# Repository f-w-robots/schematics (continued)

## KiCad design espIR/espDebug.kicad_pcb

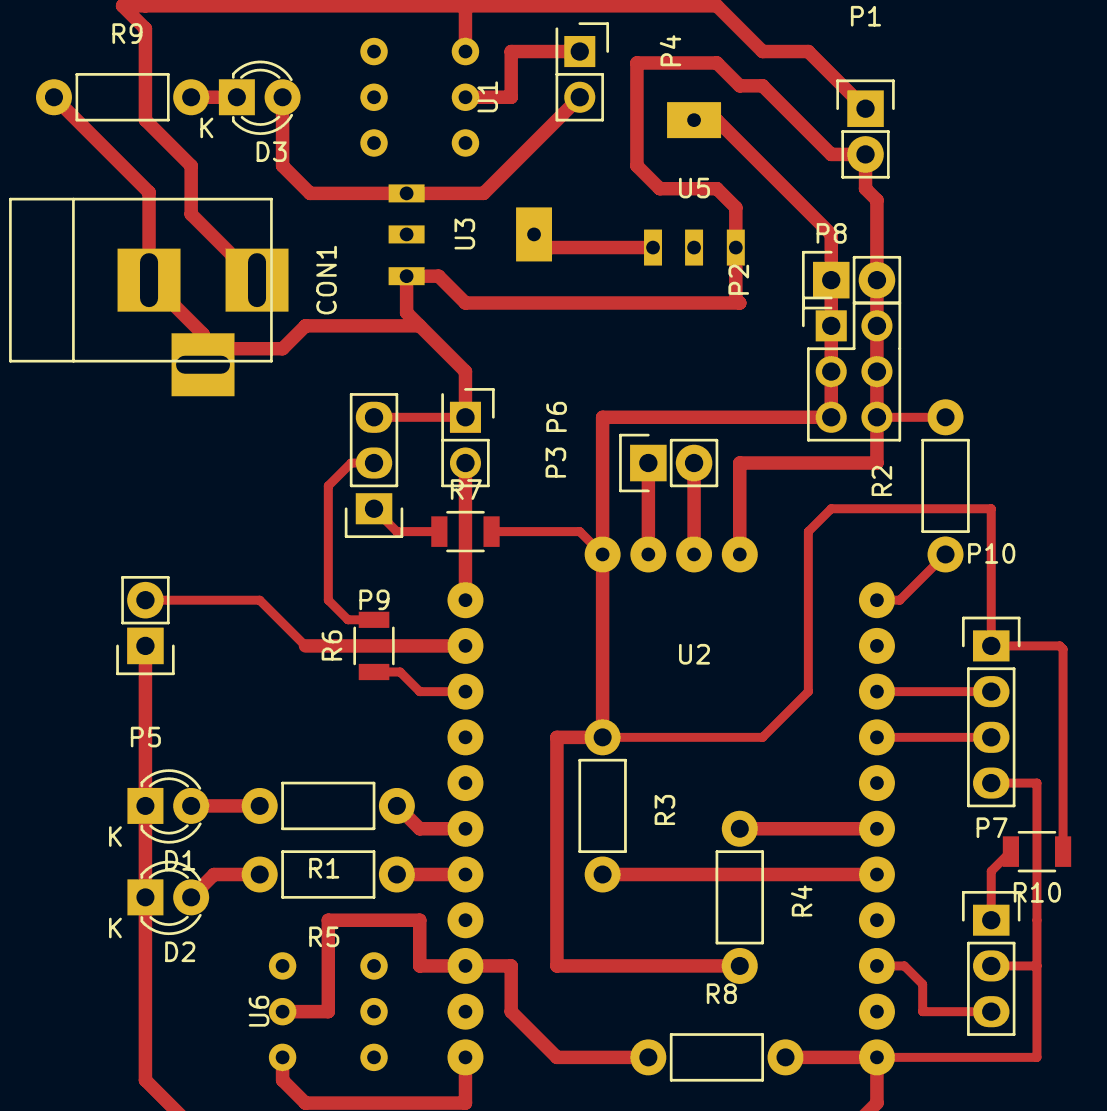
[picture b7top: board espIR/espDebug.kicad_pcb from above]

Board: 2 copper layers, 29 parts (0 on the bottom side), 28 nets.

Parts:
CON1: BARREL_JACK
D1, D2, D3: LED; LED-3MM
P1, P5: CONN_01X02; Pin_Header_Straight_1x02
P2: 3V3; Pin_Header_Straight_1x02
P3: RX/TX; Pin_Header_Straight_1x02
P4, P6: ON/OFF; Pin_Header_Straight_2x01
P7, P9: CONN_01X03; Pin_Header_Straight_1x03
P8: 3V3/GND; Pin_Header_Straight_2x03
P10: CONN_01X04; Pin_Header_Straight_1x04
R1, R5: R; Resistor_Horizontal_RM7mm
R2, R3, R4, R8: 10k; Resistor_Horizontal_RM7mm
R6, R7, R10: R; R_1206
R9: 1k; Resistor_Horizontal_RM7mm
U1: BUTTON; button
U2: ESP-201; ESP201
U3: AP1117-5; SMD-stab
U5: AP1117-3; SMD-stab
U6: button

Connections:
unnamed: CON1.1, P1.1, U1.1
unnamed: CON1.2, CON1.3, P1.2, P2.2, P6.1, P8.2, P8.4, P8.6, P9.3, R2.2, R9.1, U2.4, U3.1, U5.1
unnamed: D1.1, D2.1, P5.1, P7.2, P10.4, R8.2, U2.16
unnamed: D1.2, R1.2
unnamed: D2.2, R5.2
unnamed: D3.1, R9.2
unnamed: D3.2, P4.2, U3.3
unnamed: P3.1, U2.2
unnamed: P3.2, U2.3
unnamed: P4.1, U1.2
unnamed: P5.2, U2.6
unnamed: P6.2, U2.5
unnamed: P7.1, R10.2
unnamed: P7.3, U2.18
unnamed: P9.1, R7.1
unnamed: P9.2, R6.2
unnamed: P2.1, P8.1, P8.3, P8.5, P10.1, R3.1, R4.2, R7.2, R10.1, U2.1, U5.2
unnamed: P10.2, U2.24
unnamed: P10.3, U2.23
unnamed: R1.1, U2.10
unnamed: R2.1, U2.26
unnamed: R3.2, U2.20
unnamed: R4.1, U2.21
unnamed: R5.1, U2.11
unnamed: R6.1, U2.7
unnamed: R8.1, U2.13, U6.2
unnamed: U2.15, U6.1
unnamed: U3.2, U5.3

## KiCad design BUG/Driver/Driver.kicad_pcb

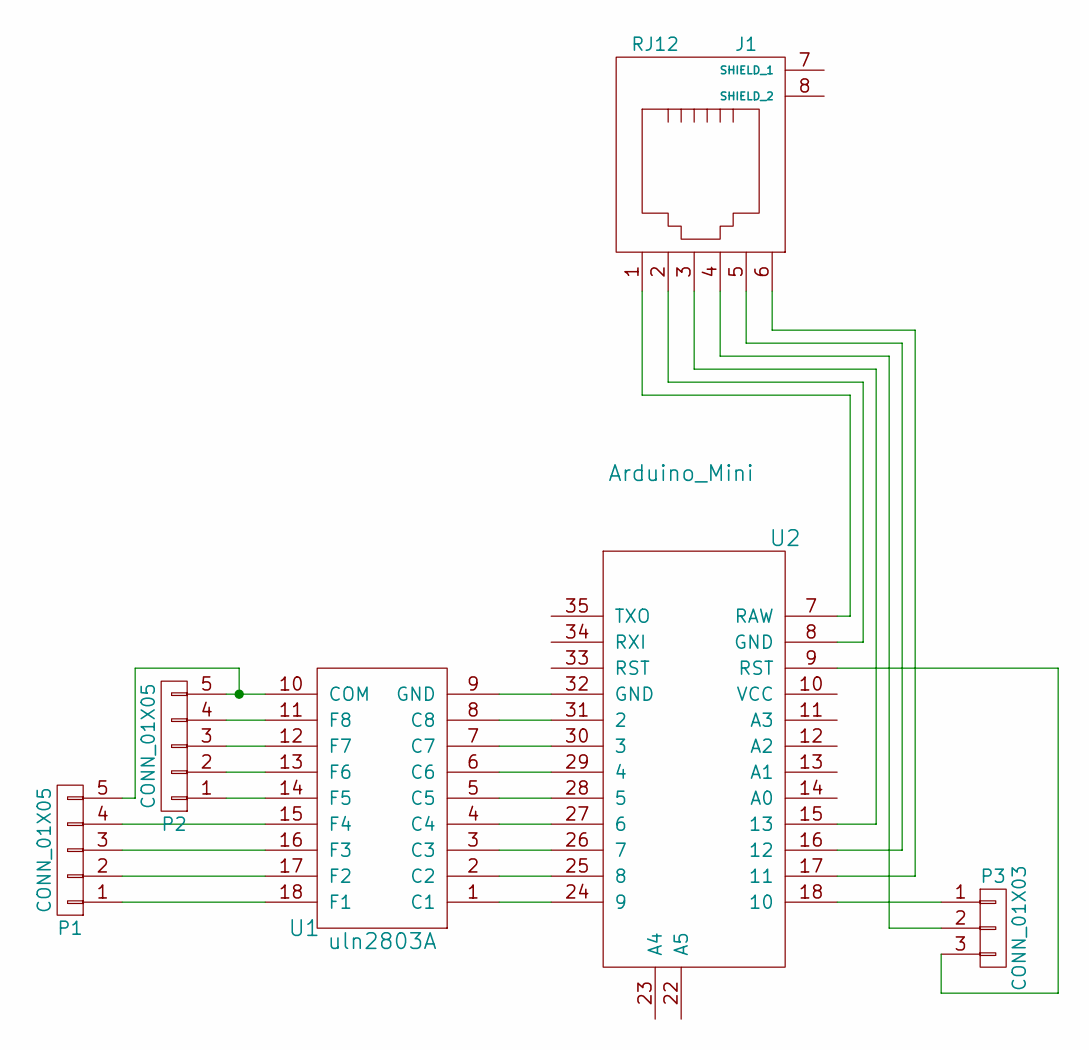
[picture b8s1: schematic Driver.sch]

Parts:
J1: RJ12; RJ12_Client
P1, P2: CONN_01X05; Pin_Header_Straight_1x05
P3: CONN_01X03; Pin_Header_Straight_1x03
U1: uln2803A; DIP-18_W7.62mm
U2: Arduino_Mini; arduino_mini_pro

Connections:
unnamed: J1.1, U2.7 (RAW)
unnamed: J1.2, U2.8 (GND)
unnamed: J1.3, U2.15 (13)
unnamed: J1.4, P3.2
unnamed: J1.5, U2.16 (12)
unnamed: J1.6, U2.17 (11)
unnamed: P1.1, U1.18 (F1)
unnamed: P1.2, U1.17 (F2)
unnamed: P1.3, U1.16 (F3)
unnamed: P1.4, U1.15 (F4)
unnamed: P1.5, P2.5, U1.10 (COM)
unnamed: P2.1, U1.14 (F5)
unnamed: P2.2, U1.13 (F6)
unnamed: P2.3, U1.12 (F7)
unnamed: P2.4, U1.11 (F8)
unnamed: P3.1, U2.18 (10)
unnamed: P3.3, U2.9 (RST)
unnamed: U1.1 (C1), U2.24 (9)
unnamed: U1.2 (С2), U2.25 (8)
unnamed: U1.3 (С3), U2.26 (7)
unnamed: U1.4 (С4), U2.27 (6)
unnamed: U1.5 (С5), U2.28 (5)
unnamed: U1.6 (С6), U2.29 (4)
unnamed: U1.7 (С7), U2.30 (3)
unnamed: U1.8 (С8), U2.31 (2)
unnamed: U1.9 (GND), U2.32 (GND)

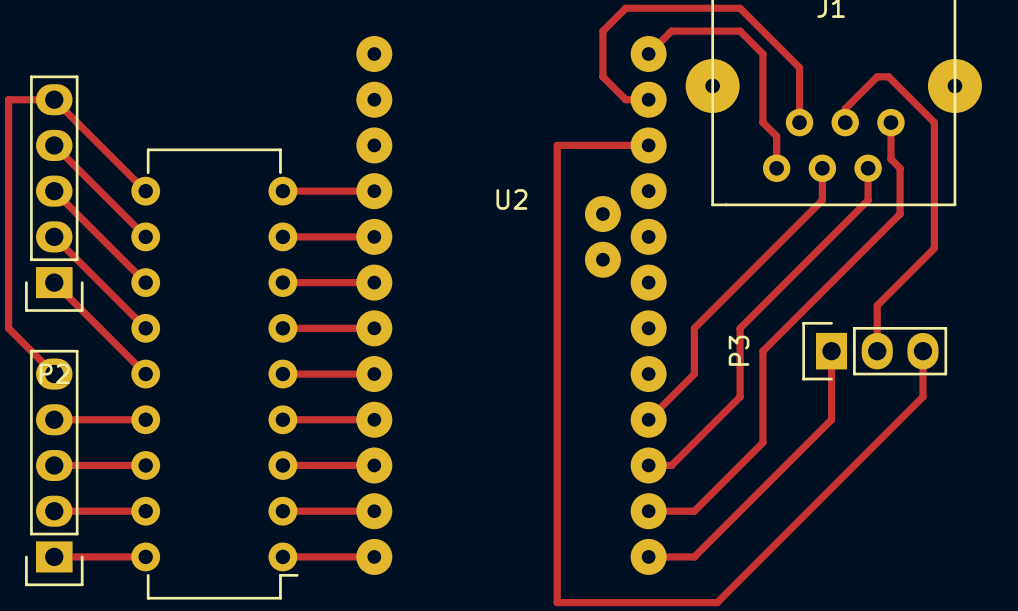
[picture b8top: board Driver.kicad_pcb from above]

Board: 2 copper layers, 6 parts (0 on the bottom side), 26 nets.

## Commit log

2016-05-25 Move schematics here
2016-05-27 CleanUp
2016-05-27 Components for BUG
2016-05-31 Added power led to marherboard
2016-06-02 Update WheelsAndIRT
2016-06-24 Schematics updates
2016-11-11 Many uodates
2017-01-17 kidkit
2017-01-17 Modified kidkit scheme
2017-01-18 Renamed some projects' folders
2017-01-18 Made PCB prototype
2017-01-19 Some fixes
2017-01-19 Jackalized a little
2017-01-21 Update Edukit
2017-02-03 Added EduKitLight
2017-02-07 Full reafactored, v 1.1
2017-02-08 Added subscriptions for PCB
2017-02-18 EduKit2
2017-02-18 Recreated EduKit project folder. Added motherboard prototype
